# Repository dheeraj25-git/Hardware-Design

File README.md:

# PCB Designs Collection  
*Open-source hardware for IoT, RF, USB, sensors, and more — designed in KiCad*

---

## Overview

A curated collection of **open-source PCB designs** for:
- **Wireless communication** (2.4 GHz, Sub-GHz, LoRa)
- **USB interfaces** (dongles, bridges, HID)
- **Microcontroller dev boards** (STM32, RP2040, ESP32)
- **Sensor modules** (IMU, environmental, RF)
- **Power & battery management**

All projects are designed in **KiCad**, fully documented, and ready for **prototyping or production**.

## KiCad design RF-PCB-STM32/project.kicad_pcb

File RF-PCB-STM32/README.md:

# STRF blueMoon — USB to 2.4 GHz nRF24L01+ Wireless Transceiver Dongle

*Compact USB-powered 2.4 GHz RF dongle with STM32 + nRF24L01+ for wireless serial, IoT, and RC applications.*

---

## Overview

**STRF** is a custom-designed USB-to-2.4GHz RF bridge combining:
- **STM32F0xx** microcontroller (LQFP32)
- **nRF24L01+** 2.4 GHz ISM band transceiver
- **SMA connector** for external antenna
- **SWD debug header**
- **USB Type-B plug** for power and data

Designed in **KiCad 9.0.1**, this board enables **wireless serial communication**, **packet sniffing**, or **IoT gateway** functionality from any USB host (PC, Raspberry Pi, etc.).

---

## Features

| Feature | Specification |
|-------|---------------|
| **MCU** | STM32F0 series |
| **RF Chip** | nRF24L01+ (2.4 GHz, 250 kbps – 2 Mbps) |
| **Interface** | USB 2.0 Full-Speed (Virtual COM Port) |
| **Antenna Port** | SMA female (50 Ω) |
| **Debug** | SWD (SWDIO, SWCLK, NRST, 3.3V, GND) |
| **Power** | USB-powered (5V → 3.3V LDO) |
| **Dimensions** | **38.25 mm × 15.75 mm** |
| **PCB Layers** | 4-layer FR4 |

---

## Block Diagram

```text
[USB Host] ←USB→ [STM32F0] ←SPI→ [nRF24L01+] ←RF→ [SMA Antenna]
                    ↑
                 [SWD Debug]

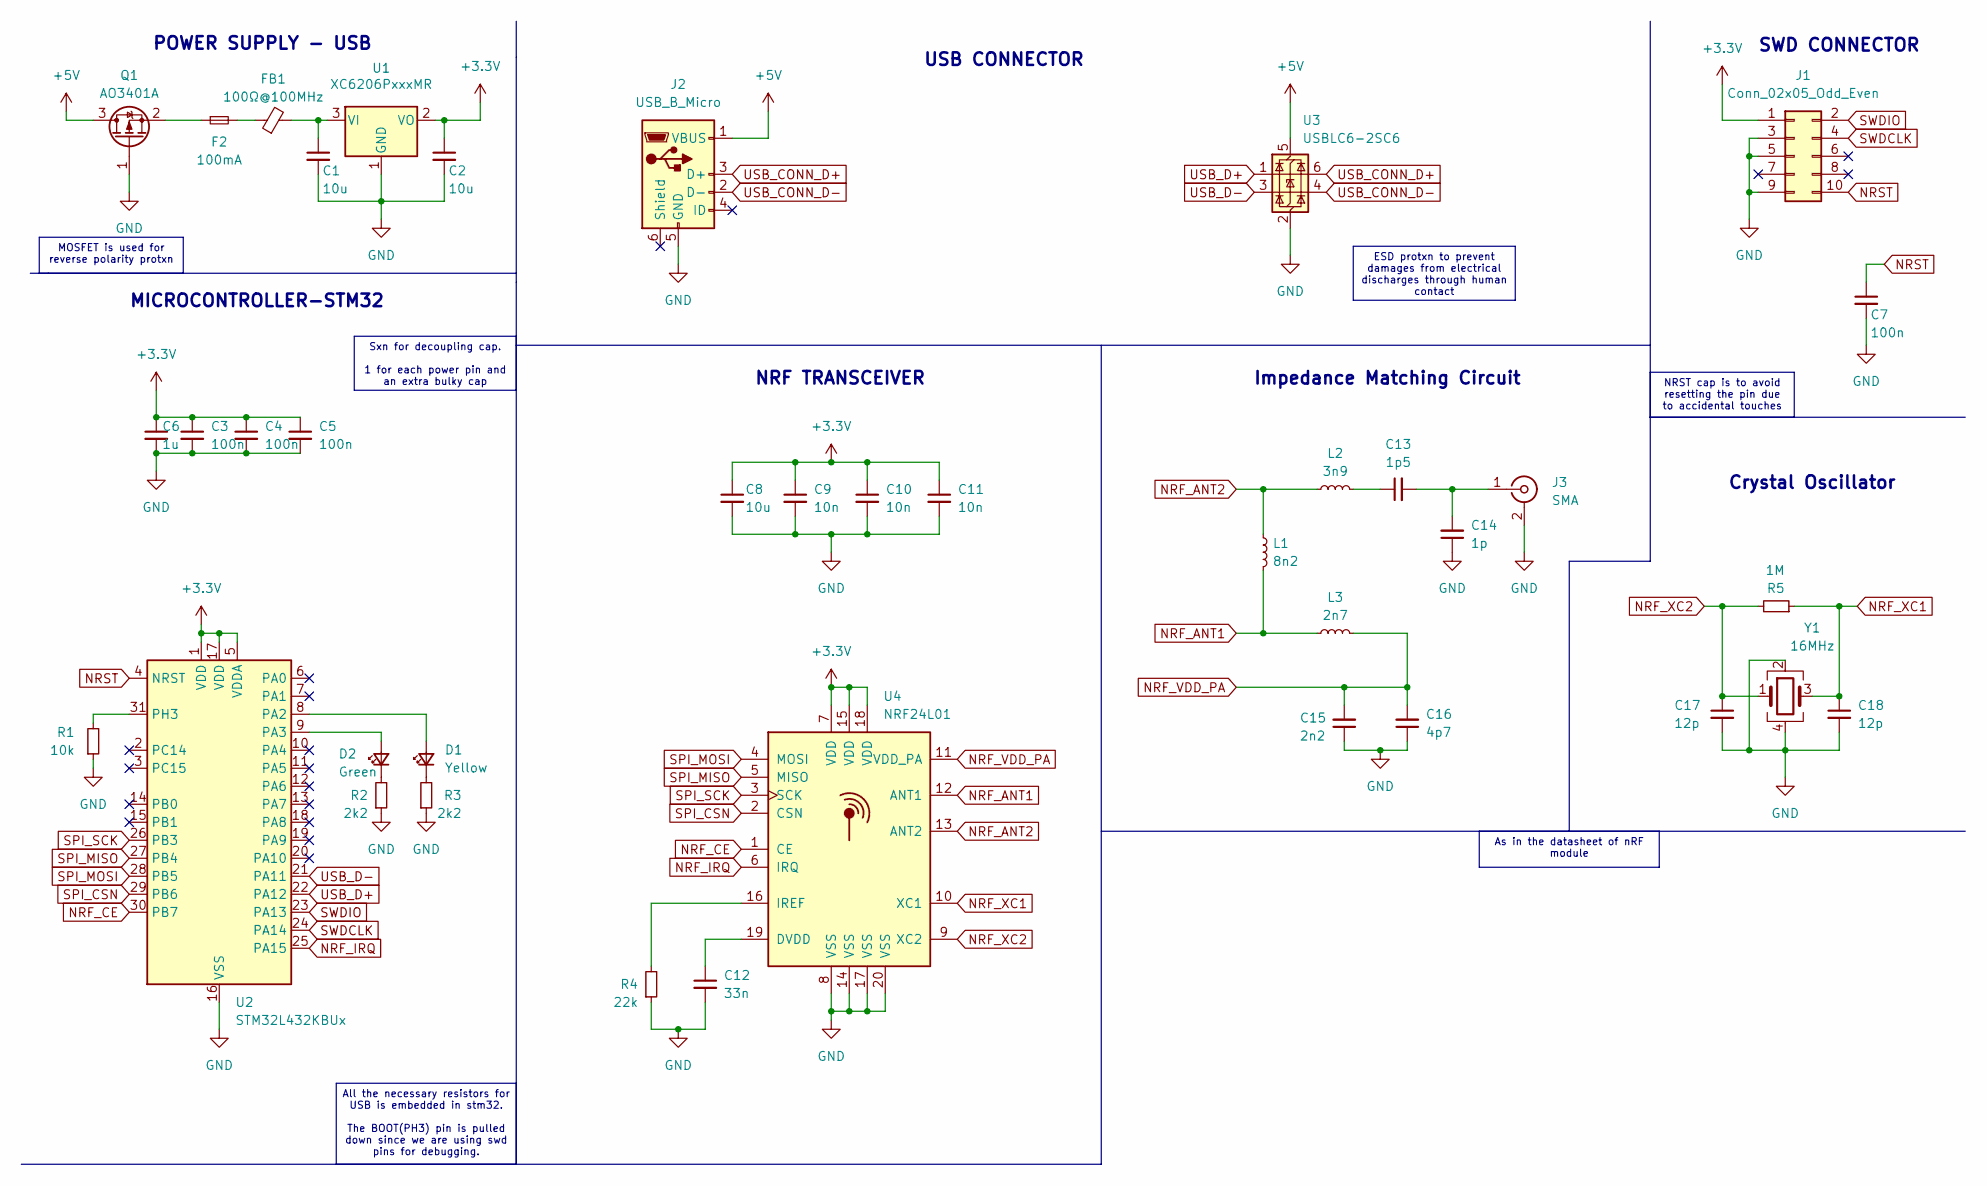
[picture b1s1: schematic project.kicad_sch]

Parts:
C1, C2: 10u; C_0603_1608Metric
C3, C4, C5, C7: 100n; C_0402_1005Metric
C6: 1u; C_0402_1005Metric
C8: 10u; C_0402_1005Metric
C9, C10, C11: 10n; C_0402_1005Metric
C12: 33n; C_0402_1005Metric
C13: 1p5; C_0402_1005Metric
C14: 1p; C_0402_1005Metric
C15: 2n2; C_0402_1005Metric
C16: 4p7; C_0402_1005Metric
C17, C18: 12p; C_0402_1005Metric
D1: Yellow; LED_0603_1608Metric
D2: Green; LED_0603_1608Metric
F2: 100mA; Fuse_1206_3216Metric
FB1: 100Ω@100MHz; L_0805_2012Metric
J1: Conn_02x05_Odd_Even; PinHeader_2x05_P1.27mm_Vertical
J2: USB_B_Micro; USB_Micro-B_Molex_47346-0001
J3: SMA; SMA_Samtec_SMA-J-P-H-ST-EM1_EdgeMount
L1: 8n2; L_0402_1005Metric
L2: 3n9; L_0402_1005Metric
L3: 2n7; L_0402_1005Metric
Q1: AO3401A; SOT-23
R1: 10k; R_0402_1005Metric
R2, R3: 2k2; R_0402_1005Metric
R4: 22k; R_0402_1005Metric_Pad0.72x0.64mm_HandSolder
R5: 1M; R_0402_1005Metric_Pad0.72x0.64mm_HandSolder
U1: XC6206PxxxMR; SOT-23-3
U2: STM32L432KBUx; QFN-32-1EP_5x5mm_P0.5mm_EP3.45x3.45mm
U3: USBLC6-2SC6; SOT-23-6
U4: NRF24L01; QFN-20-1EP_4x4mm_P0.5mm_EP2.5x2.5mm
Y1: 16MHz; Crystal_SMD_3225-4Pin_3.2x2.5mm

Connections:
+3.3V: C2.1, C3.1, C4.1, C5.1, C6.1, C8.1, C9.1, C10.1, C11.1, J1.1, U1.2 (VO), U2.1 (VDD), U2.5 (VDDA), U2.17 (VDD), U4.7 (VDD), U4.15 (VDD), U4.18 (VDD)
+5V: J2.1 (VBUS), Q1.3 (D), U3.5 (VBUS)
GND: C1.2, C2.2, C3.2, C4.2, C5.2, C6.2, C7.2, C8.2, C9.2, C10.2, C11.2, C12.2, C14.1, C15.1, C16.1, C17.2, C18.2, J1.3, J1.5, J1.9, J2.5 (GND), J3.2 (Ext), Q1.1 (G), R1.1, R2.1, R3.1, R4.1, U1.1 (GND), U2.16 (VSS), U2.32 (VSS), U2.33 (VSS), U3.2 (GND), U4.8 (VSS), U4.14 (VSS), U4.17 (VSS), U4.20 (VSS), Y1.2, Y1.4
NRF_ANT1: L1.2, L3.1, U4.12 (ANT1)
NRF_ANT2: L1.1, L2.1, U4.13 (ANT2)
NRF_CE: U2.30 (PB7), U4.1 (CE)
NRF_IRQ: U2.25 (PA15), U4.6 (IRQ)
NRF_VDD_PA: C15.2, C16.2, L3.2, U4.11 (VDD_PA)
NRF_XC1: C18.1, R5.1, U4.10 (XC1), Y1.3
NRF_XC2: C17.1, R5.2, U4.9 (XC2), Y1.1
NRST: C7.1, J1.10, U2.4 (NRST)
unnamed: C13.1, L2.2
unnamed: D1.2 (A), U2.8 (PA2)
unnamed: D1.1 (K), R3.2
unnamed: D2.2 (A), U2.9 (PA3)
unnamed: D2.1 (K), R2.2
unnamed: F2.2, FB1.1
unnamed: C13.2, C14.2, J3.1 (In)
unnamed: F2.1, Q1.2 (S)
unnamed: C1.1, FB1.2, U1.3 (VI)
unnamed: R1.2, U2.31 (PH3)
unnamed: C12.1, U4.19 (DVDD)
unnamed: R4.2, U4.16 (IREF)
SPI_CSN: U2.29 (PB6), U4.2 (CSN)
SPI_MISO: U2.27 (PB4), U4.5 (MISO)
SPI_MOSI: U2.28 (PB5), U4.4 (MOSI)
SPI_SCK: U2.26 (PB3), U4.3 (SCK)
SWDCLK: J1.4, U2.24 (PA14)
SWDIO: J1.2, U2.23 (PA13)
USB_CONN_D+: J2.3 (D+), U3.6 (I/O1)
USB_CONN_D-: J2.2 (D-), U3.4 (I/O2)
USB_D+: U2.22 (PA12), U3.1 (I/O1)
USB_D-: U2.21 (PA11), U3.3 (I/O2)

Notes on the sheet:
As in the datasheet of nRF module
MOSFET is used for reverse polarity protxn
ESD protxn to prevent damages from electrical discharges through human contact
NRST cap is to avoid resetting the pin due to accidental touches
Sxn for decoupling cap. 1 for each power pin and an extra bulky cap
All the necessary resistors for USB is embedded in stm32. The BOOT(PH3) pin is pulled down since we are using swd pins for debugging.
USB CONNECTOR
POWER SUPPLY - USB
MICROCONTROLLER-STM32
Impedance Matching Circuit
Crystal Oscillator
NRF TRANSCEIVER
SWD CONNECTOR

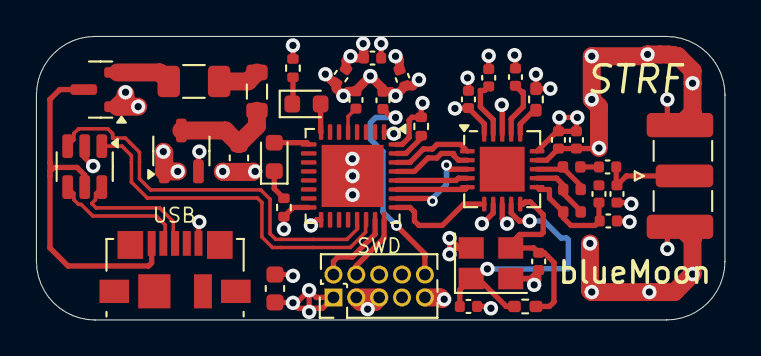
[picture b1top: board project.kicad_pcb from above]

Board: 4 copper layers, 38.2 x 15.8 mm, 39 parts (0 on the bottom side), 33 nets.

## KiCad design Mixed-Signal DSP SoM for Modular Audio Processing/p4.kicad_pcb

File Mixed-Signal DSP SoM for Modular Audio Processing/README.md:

# 🎛️ **High-Performance Audio DSP System on Module (SoM)**  
### *Real-Time Mixed-Signal Platform for Modular Audio Processing*

## 🚀 **Overview**

A **compact, production-ready 40x40mm System on Module (SoM)** designed for **high-fidelity, real-time digital audio processing**. Built around the **STM32H7 (480 MHz Cortex-M7 + FPU/DSP)**, this modular platform enables **plug-and-play audio effects** (reverb, delay, distortion, EQ) via interchangeable **Daughterboards (Carrier Boards)**.

> **"Design once. Process everything."** 🎸🎤

---

## 🛠 **Tech Stack**

| Category              | Technology / Component                                 |
|-----------------------|--------------------------------------------------------|
| **MCU**               | STM32H743xI/G – 480 MHz, 2MB Flash, 1MB RAM, FPU + DSP |
| **Audio Codec**       | Integrated ADC/DAC + 4x SAI (Serial Audio Interface)   |
| **PCB**               | 4-Layer (Sig-GND-GND-Sig)                              |
| **High-Speed I/O**    | 2x USB OTG HS/FS (crystal-less), 2x SDIO (125 MHz)     |
| **Power**             | 3.3V Digital + 1.8V Analog (isolated rails)            |
| **Debug**             | SWD via Tag-Connect (solderless), 24 MHz XTAL          |
| **Tools**             | STM32CubeIDE, STM32CubeMX                              |

---

## ✨ **Key Features**

- **Modular Mezzanine Interface**  
  → Reuse core SoM across guitar pedals, vocal processors, synths

- **Ultra-Low Noise Mixed-Signal Design**  
  - Physical **analog/digital separation**  
  - Pi-filter + ferrite beads on 1.8V analog rail  
  - 100 nF decoupling **per VDD/VBAT pin**

- **Pro-Grade Signal Integrity**  
  - Series resistor on SDIO CLK (EMI/ringing control)  
  - Dedicated **GND return per signal pin** on connector  
  - ESD-protected inputs + 2.2 kΩ I²C pull-ups

- **Real-Time DSP Engine**  
  - 480 MHz processing for **reverb, delay, overdrive, filters**  
  - Double-precision FPU + CMSIS-DSP optimized

---

## 📂 **Repository Structure**

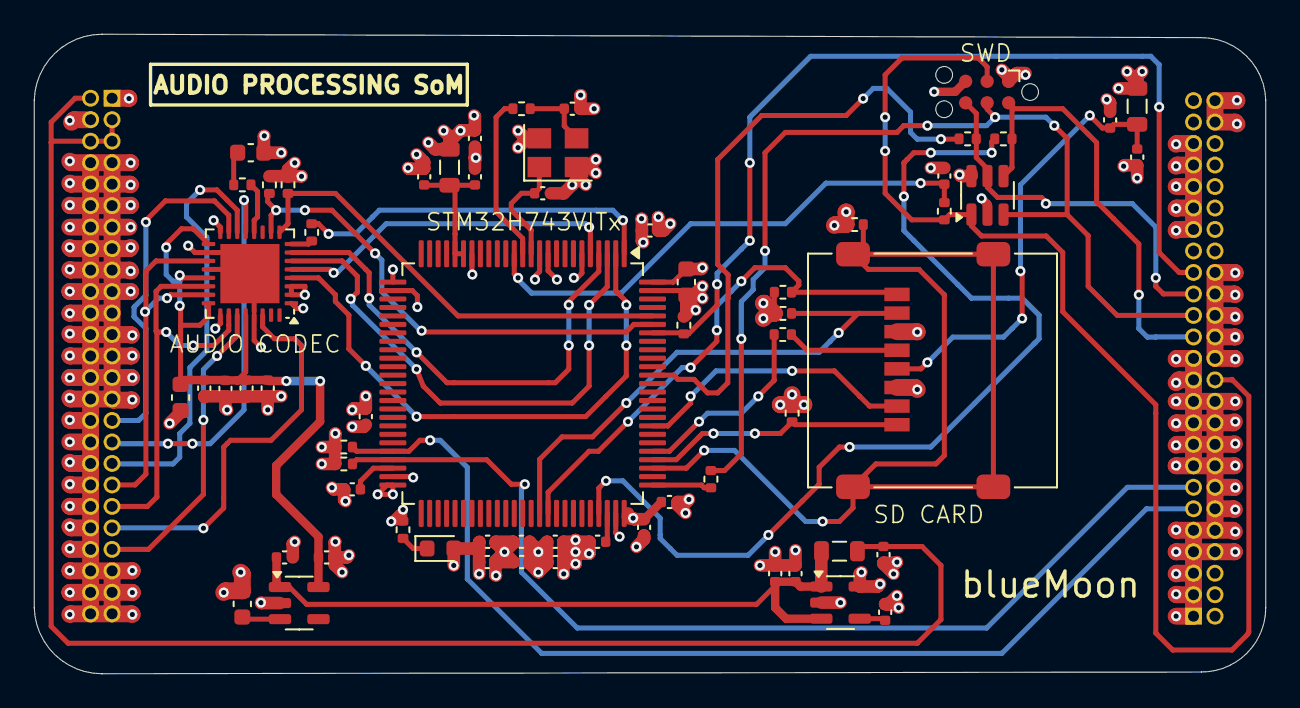
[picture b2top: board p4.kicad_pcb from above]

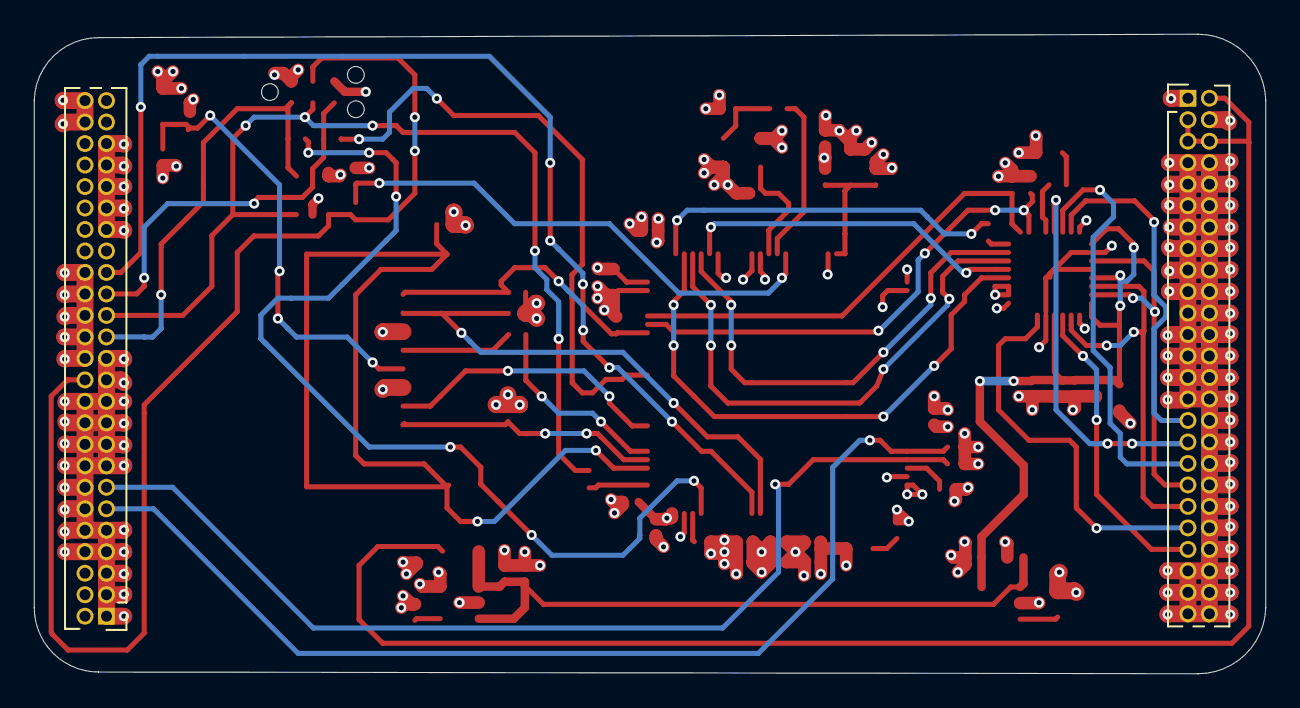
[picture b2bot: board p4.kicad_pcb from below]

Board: 4 copper layers, 72.8 x 37.8 mm, 66 parts (2 on the bottom side), 50 nets.

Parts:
C1, C32: 4u7; C_0603_1608Metric
C2, C3, C4, C5, C7, C8, C9, C10, C11, C12, C15, C16, C17, C18, C19, C25, C28, C30, C31: 100n; C_0402_1005Metric
C6, C23: 2u2; C_0603_1608Metric
C13, C14, C20, C26, C27, C29, C33, C34: 2u2; C_0402_1005Metric
C21: 470p; C_0402_1005Metric
C22, C24: 1u; C_0402_1005Metric
D1: SP0505BAHT; SOT-23-6
D2: LED_Small; LED_0603_1608Metric
FB1: 100 Ω; L_0805_2012Metric
FB2, FB3: 100Ω; L_0805_2012Metric
J1: Conn_ARM_SWD_TagConnect_TC2030-NL; Tag-Connect_TC2030-IDC-NL_2x03_P1.27mm_Vertical
J2: SD_Card_Device; microSD_HC_Molex_47219-2001
J3, J4: Conn_02x25_Counter_Clockwise; PinHeader_2x25_P1.27mm_Vertical
R1, R14: 49R9; R_0402_1005Metric
R2: 49R9 Ω; R_0402_1005Metric
R3: 10kΩ; R_0402_1005Metric
R4, R5, R6, R7, R8, R9: 1K; R_0402_1005Metric
R10, R11, R12, R13: 10k; R_0402_1005Metric
R15, R16, R17, R18: 2K2; R_0402_1005Metric
U1: TLV320AIC3100; VQFN-32-1EP_5x5mm_P0.5mm_EP3.5x3.5mm
U3: STM32H743VITx; LQFP-100_14x14mm_P0.5mm
U4: MIC5219-3.3YM5; SOT-23-5
U5: MIC5317-1.8xM5; SOT-23-5
Y1: 24MHz; Crystal_SMD_3225-4Pin_3.2x2.5mm

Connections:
+1V8: C1.1, C2.1, C3.1, C4.1, C5.1, C24.1, U1.17 (AVDD), U1.21 (SPKVDD), U1.24 (SPKVDD), U1.28 (HPVDD), U5.5 (VOUT)
+3V3: C6.1, C7.1, C8.1, C9.1, C10.1, C11.1, C12.1, C15.1, C26.1, C29.1, C30.1, C31.1, D1.6 (K), D2.2 (A), FB1.1, FB2.1, J1.1 (VCC), R10.1, R11.1, R12.1, R13.1, R15.1, R16.1, R17.1, R18.1, U1.2 (IOVDD), U1.3 (DVDD), U3.6 (VBAT), U3.11 (VDD), U3.27 (VDD), U3.50 (VDD), U3.75 (VDD), U3.100 (VDD), U4.5 (OUT)
+5V: C20.1, C22.1, C33.1, FB3.2, U4.1 (IN), U4.3 (EN), U5.1 (VIN)
/BOOT0: J3.33, R3.1, U3.94 (BOOT0)
/HPL: J4.43, U1.27 (HPL)
/HPR: J4.41, U1.30 (HPR)
/I2C1_SCL: R15.2, U1.10 (SCL), U3.95 (PB8)
/I2C1_SDA: R16.2, U1.9 (SDA), U3.96 (PB9)
/I2C2_SCL: J3.11, R17.2, U3.46 (PB10)
/I2C2_SDA: J3.13, R18.2, U3.47 (PB11)
/MICROCONTROLLER (STM32)/HSE_IN: C18.1, U3.12 (PH0), Y1.1
/MICROCONTROLLER (STM32)/HSE_OUT: R2.2, U3.13 (PH1)
/MIC_IN: J4.31, U1.15 (MIC1LM)
/MIC_LP: J4.33, U1.13 (MIC1LP)
/MIC_RP: J4.35, U1.14 (MIC1RP)
/NRST: D1.1 (K), J1.3 (~RESET), J3.24, R5.1
/NRST_mcu: C25.1, R5.2, U3.14 (NRST)
/SAI1_DIN_A: U1.5 (DIN), U3.5 (PE6)
/SAI1_DOUT_B: U1.4 (DOUT), U3.2 (PE3)
/SAI1_FS_A: U1.6 (WCLK), U3.3 (PE4)
/SAI1_MCLK_A: R1.1, U3.1 (PE2)
/SAI1_SCK_A: U1.7 (BCLK), U3.4 (PE5)
/SDMMC1 CLK: R9.2, U3.80 (PC12)
/SDMMC1 CMD: J2.2 (CMD), U3.83 (PD2)
/SDMMC1 D0: J2.7 (DAT0), R10.2, U3.65 (PC8)
/SDMMC1 D1: J2.8 (DAT1), R11.2, U3.66 (PC9)
/SDMMC1 D2: J2.9 (DAT2), R12.2, U3.78 (PC10)
/SDMMC1 D3: J2.1 (CD/DAT3), R13.2, U3.79 (PC11)
/SPKM: J4.37, U1.19 (SPKM), U1.23 (SPKM)
/SPKP: J4.39, U1.22 (SPKP), U1.26 (SPKP)
/SWCLK: D1.3 (K), J1.4 (SWCLK), J3.29, R6.1
/SWCLK_mcu: R6.2, U3.76 (PA14)
/SWDIO: D1.4 (K), J1.2 (SWDIO), J3.27, R7.1
/SWDIO_mcu: R7.2, U3.72 (PA13)
/SWO: D1.5 (K), J1.6 (SWO), J3.31, R8.1
/SWO_mcu: R8.2, U3.89 (PB3)
GND: C1.2, C2.2, C3.2, C4.2, C5.2, C6.2, C7.2, C8.2, C9.2, C10.2, C11.2, C12.2, C13.2, C14.2, C15.2, C16.1, C17.1, C18.2, C19.2, C20.2, C21.2, C22.2, C23.2, C24.2, C25.2, C26.2, C27.2, C28.2, C29.2, C30.2, C31.2, C32.2, C33.2, C34.2, D1.2 (A), J1.5 (GND), J2.3 (VSS), J2.6 (VSS), J3.1, J3.3, J3.5, J3.7, J3.8, J3.9, J3.10, J3.12, J3.14, J3.15, J3.16, J3.17, J3.18, J3.19, J3.20, J3.21, J3.22, J3.23, J3.25, J3.26, J3.28, J3.30, J3.32, J3.34, J3.37, J3.39, J3.41, J3.43, J3.45, J3.48, J3.50, J4.1, J4.4, J4.7, J4.8, J4.9, J4.10, J4.11, J4.12, J4.13, J4.14, J4.15, J4.16, J4.17, J4.18, J4.19, J4.20, J4.21, J4.22, J4.23, J4.24, J4.25, J4.26, J4.27, J4.28, J4.29, J4.30, J4.32, J4.34, J4.36, J4.38, J4.40, J4.42, J4.44, J4.45, J4.46, J4.47, J4.48, J4.49, J4.50, R3.2, R4.2, U1.1 (IOVSS), U1.16 (AVSS), U1.18 (DVSS), U1.20 (SPKVSS), U1.25 (SPKVSS), U1.29 (HPVSS), U1.33 (EP), U3.10 (VSS), U3.19 (VSSA), U3.26 (VSS), U3.49 (VSS), U3.74 (VSS), U3.99 (VSS), U4.2 (GND), U5.2 (GND), Y1.2, Y1.4
unnamed: C13.1, U3.48 (VCAP)
unnamed: C14.1, U3.73 (VCAP)
unnamed: C19.1, R2.1, Y1.3
unnamed: C32.1, R14.2
unnamed: D2.1 (K), R4.1
unnamed: J2.5 (CLK), R9.1
unnamed: C27.1, C28.1, FB2.2, J2.4 (VDD)
unnamed: C34.1, FB3.1, J4.2, J4.3, J4.5, J4.6
unnamed: R1.2, U1.8 (MCLK)
unnamed: R14.1, U1.12 (MICBIAS)
unnamed: C21.1, U4.4 (BP)
unnamed: C23.1, U5.3 (EN)
VDDA: C16.2, C17.2, FB1.2, U3.20 (VREF+), U3.21 (VDDA)

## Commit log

2025-10-31 Create board
2025-10-31 Create KiCad files
2025-10-31 Create images
2025-10-31 Create Mixed-Signal DSP SoM for Modular Audio Processing
2025-10-31 Create b1
2025-10-31 Add README for High-Performance Audio DSP SoM
    Added detailed README for the High-Performance Audio DSP SoM project, including overview, tech stack, key features, and repository structure.
2025-11-14 Create RF-PCB-DESIGN-STM32
